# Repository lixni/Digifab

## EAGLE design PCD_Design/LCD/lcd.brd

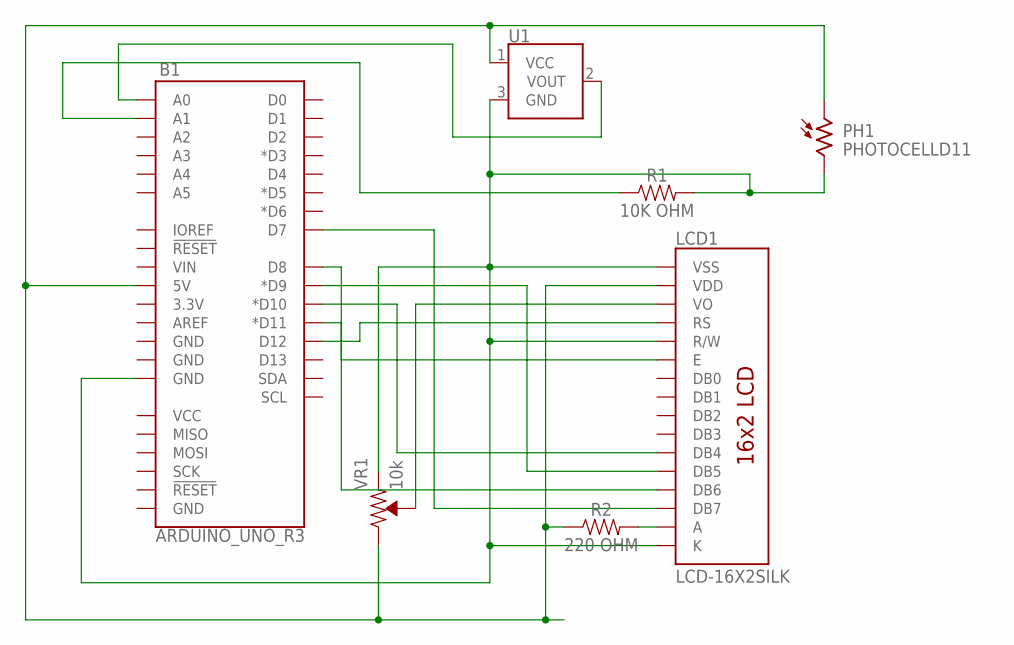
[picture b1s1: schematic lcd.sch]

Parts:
B1: ARDUINO_UNO_R3; ARDUINO_R3
LCD1: LCD-16X2SILK; LCD-16X2
PH1: PHOTOCELLD11; D11XX_H
R1: 10K OHM; AXIAL-0.3
R2: 220 OHM; AXIAL-0.3
U1: TMP36GT9; TO-92
VR1: 10k; TRIMPOT-PTH-3386U

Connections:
unnamed: B1.A1, R1.P$1 (1)
unnamed: B1.A0, U1.2 (VOUT)
unnamed: B1.5V, LCD1.2 (VDD), PH1.1, R2.P$1 (1), U1.1 (VCC), VR1.3 (CW)
unnamed: B1.GND@2 (GND), LCD1.1 (VSS), LCD1.5 (R/W), LCD1.16 (K), PH1.2, R1.P$2 (2), U1.3 (GND), VR1.1 (CCW)
unnamed: LCD1.3 (VO), VR1.2 (WIPER)
unnamed: LCD1.15 (A), R2.P$2 (2)
unnamed: B1.D7, LCD1.14 (DB7)
unnamed: B1.D12, LCD1.4 (RS)
unnamed: B1.D11 (*D11), LCD1.6 (E)
unnamed: B1.D9 (*D9), LCD1.12 (DB5)
unnamed: B1.D8, LCD1.13 (DB6)
unnamed: B1.D10 (*D10), LCD1.11 (DB4)

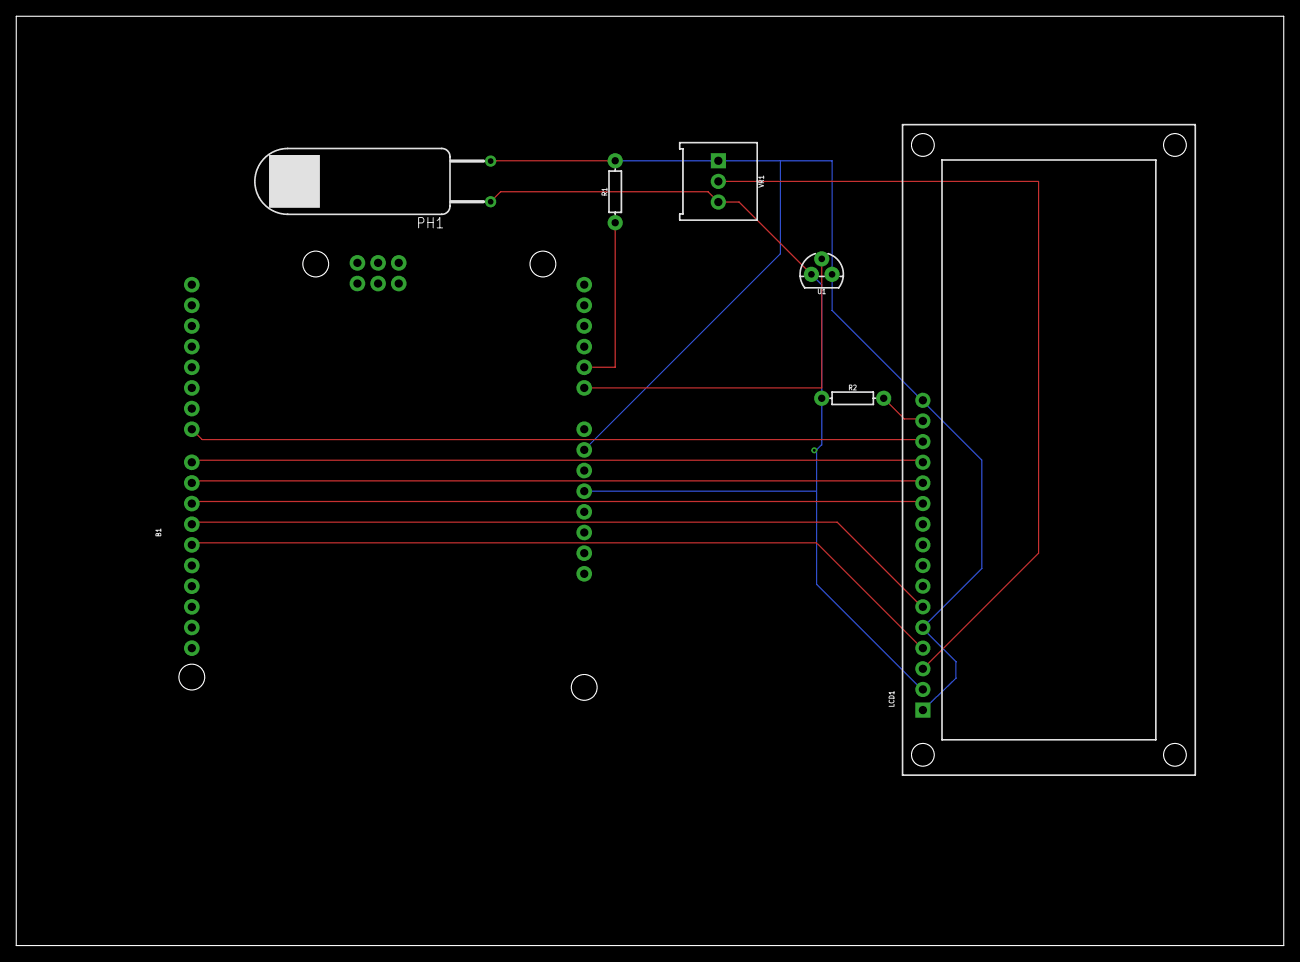
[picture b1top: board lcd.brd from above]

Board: 2 copper layers, 155.9 x 114.3 mm, 7 parts (0 on the bottom side), 12 nets.

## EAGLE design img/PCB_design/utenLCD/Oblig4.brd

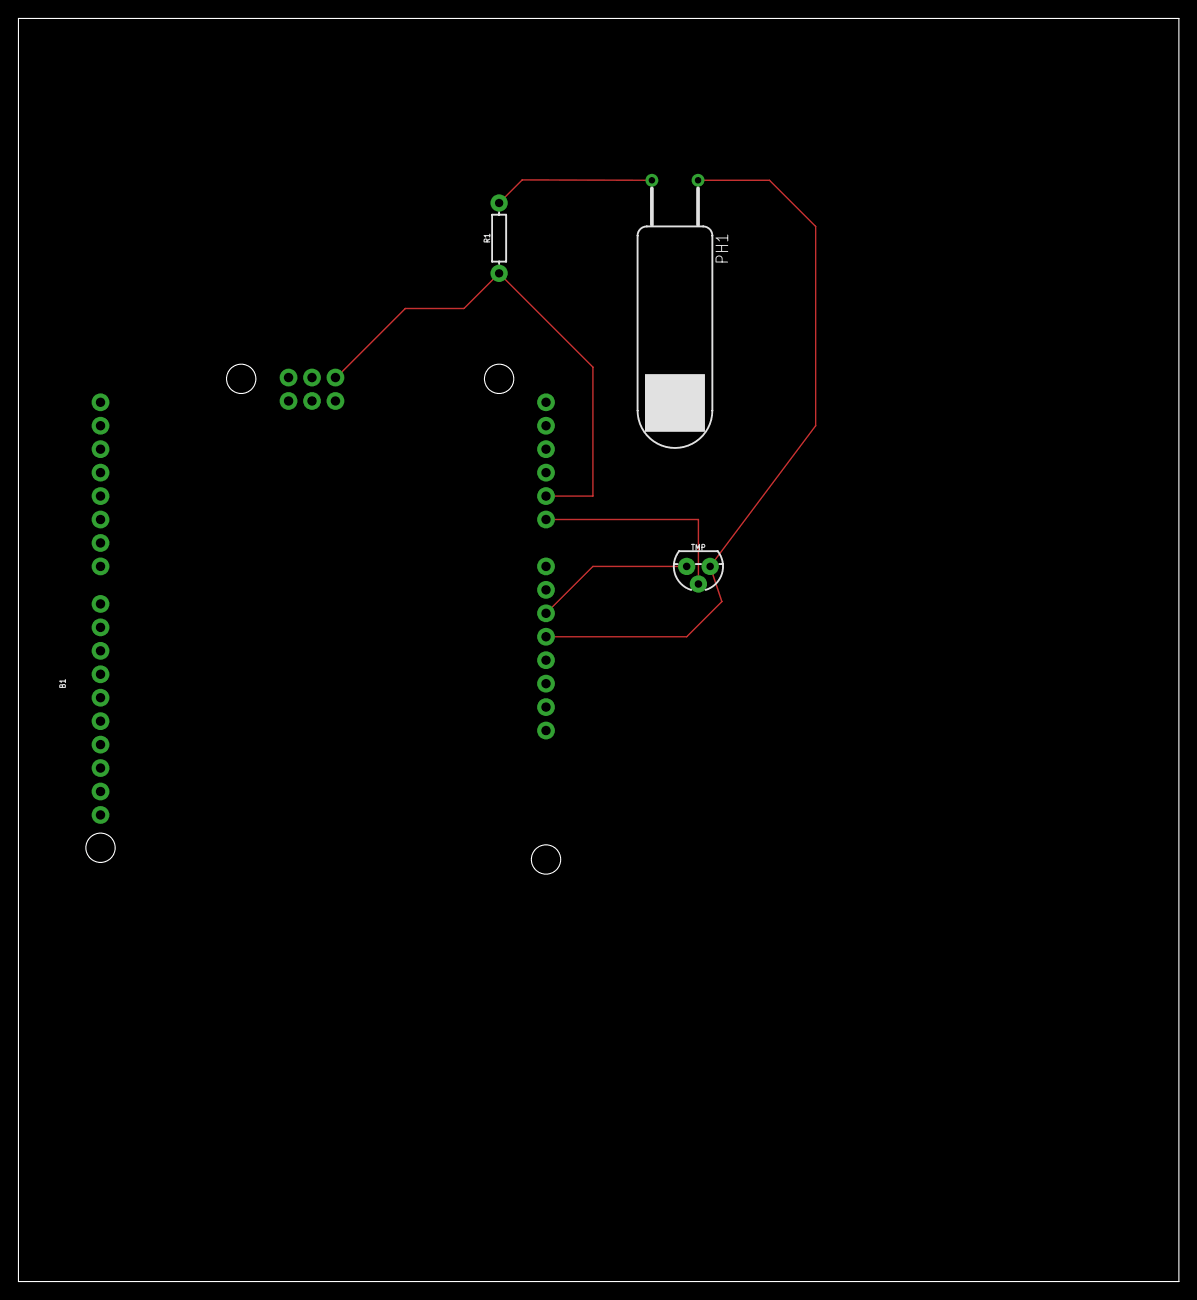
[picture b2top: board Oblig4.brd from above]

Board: 2 copper layers, 125.7 x 136.8 mm, 4 parts (0 on the bottom side), 5 nets.

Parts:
B1: ARDUINO_UNO_R3; ARDUINO_R3
PH1: PHOTOCELLD11; D11XX_H
R1: 220 OHM; AXIAL-0.3
TMP: TO-92

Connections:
unnamed: PH1.2, R1.P$2
unnamed: B1.5V, PH1.1, TMP.1
S$1: B1.A1, B1.GND@4, R1.P$1
S$2: B1.A0, TMP.2
S$3: B1.GND@1, TMP.3

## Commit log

2022-09-30 icon
2022-09-30 lagt til prosjekt sider
2022-10-01 added om meg
2022-10-01 fikset skrivefeil
2022-10-01 skrivfeil meny
2022-10-02 added about me and darkmode
2022-10-02 background header fixed
2022-11-09 lagt til bilde, lagt litt tekst og stl/fusion/mp4
2022-11-18 3dprint final
2022-11-18 rettet skrivefeil
2023-02-26 Oblig 3
2023-03-26 Oblig4
2023-03-26 oppdatert oblig 4 pcd_design.html
2023-03-26 Oppdatert
2023-03-26 lagt til link
2023-03-26 lagt til txt og zip filer
2023-03-26 fjernet txt
2023-03-26 flytet koblingene
2023-03-26 lagt til mellomrom
2023-03-26 endret txt
2023-03-26 manglet en kobling
2023-03-26 oppdatert lcd filene
2023-03-26 Lagt til E - D11
2023-05-30 sluttprosjekt
2023-05-30 endre link farge
2023-05-30 endret skrivefeil
2023-05-30 la til txt
2023-05-30 skrivefeil

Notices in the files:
parts and their libraries:
SparkFun-Boards: Licensing: Creative Commons ShareAlike 4.0 International - https://creativecommons.org/licenses/by-sa/4.0
